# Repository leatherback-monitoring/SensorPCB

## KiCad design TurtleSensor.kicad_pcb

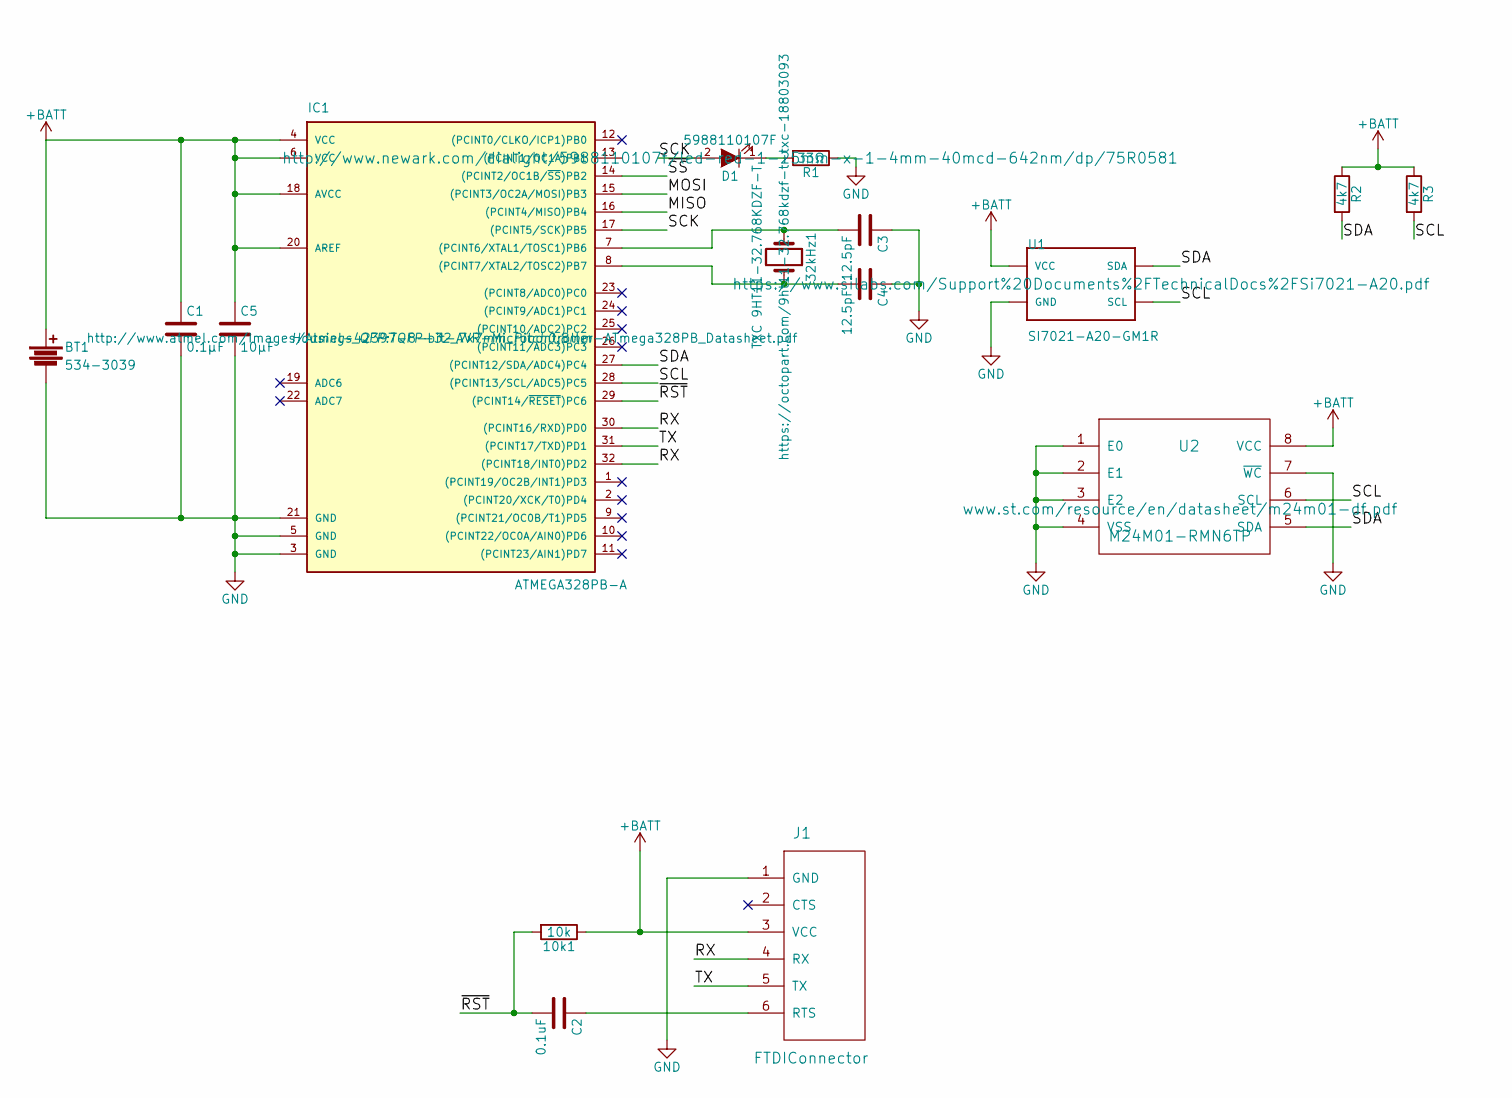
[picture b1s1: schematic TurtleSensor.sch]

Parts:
10k1: 10k; R_0805_HandSoldering
32kHz1: TXC 9HT11-32.768KDZF-T; R_0805_HandSoldering
BT1: 534-3039; 2477Holder
C1: 0.1µF; C_0805_HandSoldering
C2: 0.1uF; C_0805_HandSoldering
C3, C4: 12.5pF; C_0805_HandSoldering
C5: 10µF; C_0805_HandSoldering
D1: 5988110107F; LED_0805
IC1: ATMEGA328PB-A; TQFP-32_7x7mm_Pitch0.8mm
J1: FTDIConnector; Pin_Header_Straight_1x06_Pitch2.54mm
R1: 33Ω; R_0805_HandSoldering
R2, R3: 4k7; R_0805_HandSoldering
U1: SI7021-A20-GM1R; DFN-6%2f3MM
U2: M24M01-RMN6TP; SOIC-8-N

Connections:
+BATT: 10k1.1, BT1.1, C1.1, C5.1, IC1.4 (VCC), IC1.6 (VCC), IC1.18 (AVCC), IC1.20 (AREF), J1.3 (VCC), R2.1, R3.1, U1.5 (VCC), U2.8 (VCC)
/MISO: IC1.16 ((PCINT4/MISO)PB4)
/MOSI: IC1.15 ((PCINT3/OC2A/MOSI)PB3)
/RX: IC1.30 ((PCINT16/RXD)PD0), IC1.32 ((PCINT18/INT0)PD2), J1.4 (RX)
/SCK: D1.2 (A), IC1.17 ((PCINT5/SCK)PB5)
/SCL: IC1.28 ((PCINT13/SCL/ADC5)PC5), R3.2, U1.6 (SCL), U2.6 (SCL)
/SDA: IC1.27 ((PCINT12/SDA/ADC4)PC4), R2.2, U1.1 (SDA), U2.5 (SDA)
/TX: IC1.31 ((PCINT17/TXD)PD1), J1.5 (TX)
/~RST: 10k1.2, C2.2, IC1.29 ((PCINT14/~RESET~)PC6)
/~SS: IC1.14 ((PCINT2/OC1B/~SS~)PB2)
GND: BT1.2, C1.2, C3.1, C4.1, C5.2, IC1.3 (GND), IC1.5 (GND), IC1.21 (GND), J1.1 (GND), R1.1, U1.2 (GND), U2.1 (E0), U2.2 (E1), U2.3 (E2), U2.4 (VSS), U2.7 (~WC)
unnamed: 32kHz1.1, C3.2, IC1.7 ((PCINT6/XTAL1/TOSC1)PB6)
unnamed: 32kHz1.2, C4.2, IC1.8 ((PCINT7/XTAL2/TOSC2)PB7)
unnamed: C2.1, J1.6 (RTS)
unnamed: D1.1 (K), R1.2

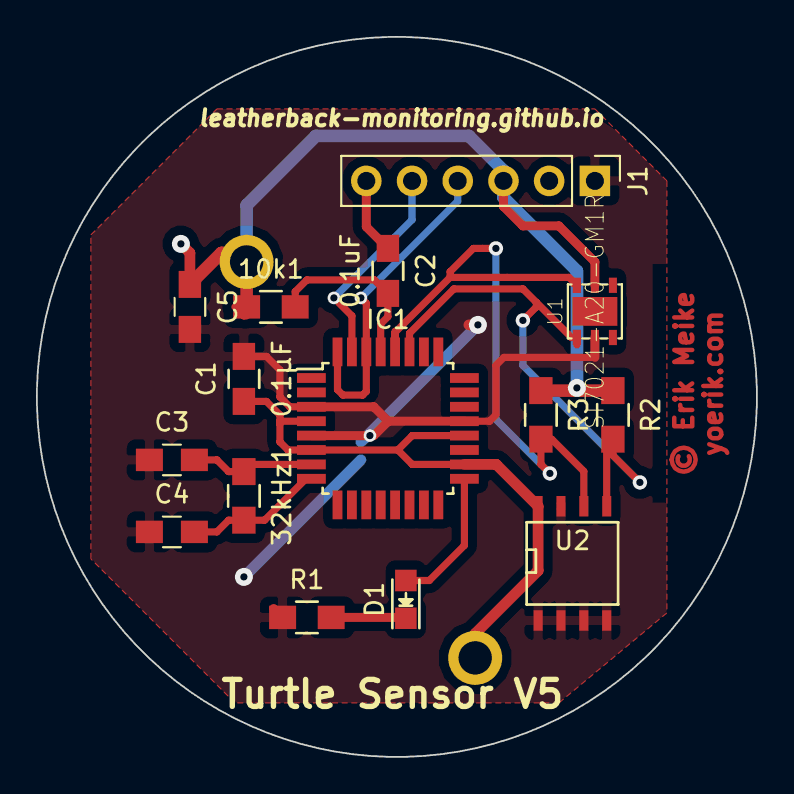
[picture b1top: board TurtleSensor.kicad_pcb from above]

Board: 2 copper layers, 40.0 x 40.0 mm, 16 parts (1 on the bottom side), 12 nets.

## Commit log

2016-03-16 updated some footprints
2016-03-20 added copyright
2016-04-17 mostly routed
2016-04-30 pads underneath flash short
2016-06-13 switching to new components
2016-06-13 added footprints
2016-06-26 added missing pullups and lots
2016-07-04 rerouted and made board
2016-07-04 created battery holder footprint
2016-07-09 sent board to be manufactured
2016-07-12 imported dxf
2016-09-12 fixed programming resistor, pcb is now circular v4
2016-09-12 update gitignore
2016-09-19 before copper fill
2016-09-19 rotated capacitor to be parallel
2017-01-25 rerouted power
2017-01-25 rev5

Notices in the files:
TurtleSensor.kicad_pcb:
© Erik Meike
